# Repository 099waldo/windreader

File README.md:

# WindReader

WindReader is a Raspberry Pi hat for reading sensor data from the NRG #40 Anemometer and the NRG 200P direction vane from NRG Systems. 

It uses the popular LM741 op amp as well as the MCP3008 analog to digital converter in order to send the analog sensor readings 
to the Raspberry Pi.

The project started when I scored some free wind sensors from an old weather station. It seemed like the perfect opprotunity to try 
my hand at pcb design! 

Unfortunatly, upon further inspection, the only direction vane I got didn't work but in theory the circuit should work fine. 
If I am able to get my hands on a working one I will confirm this.

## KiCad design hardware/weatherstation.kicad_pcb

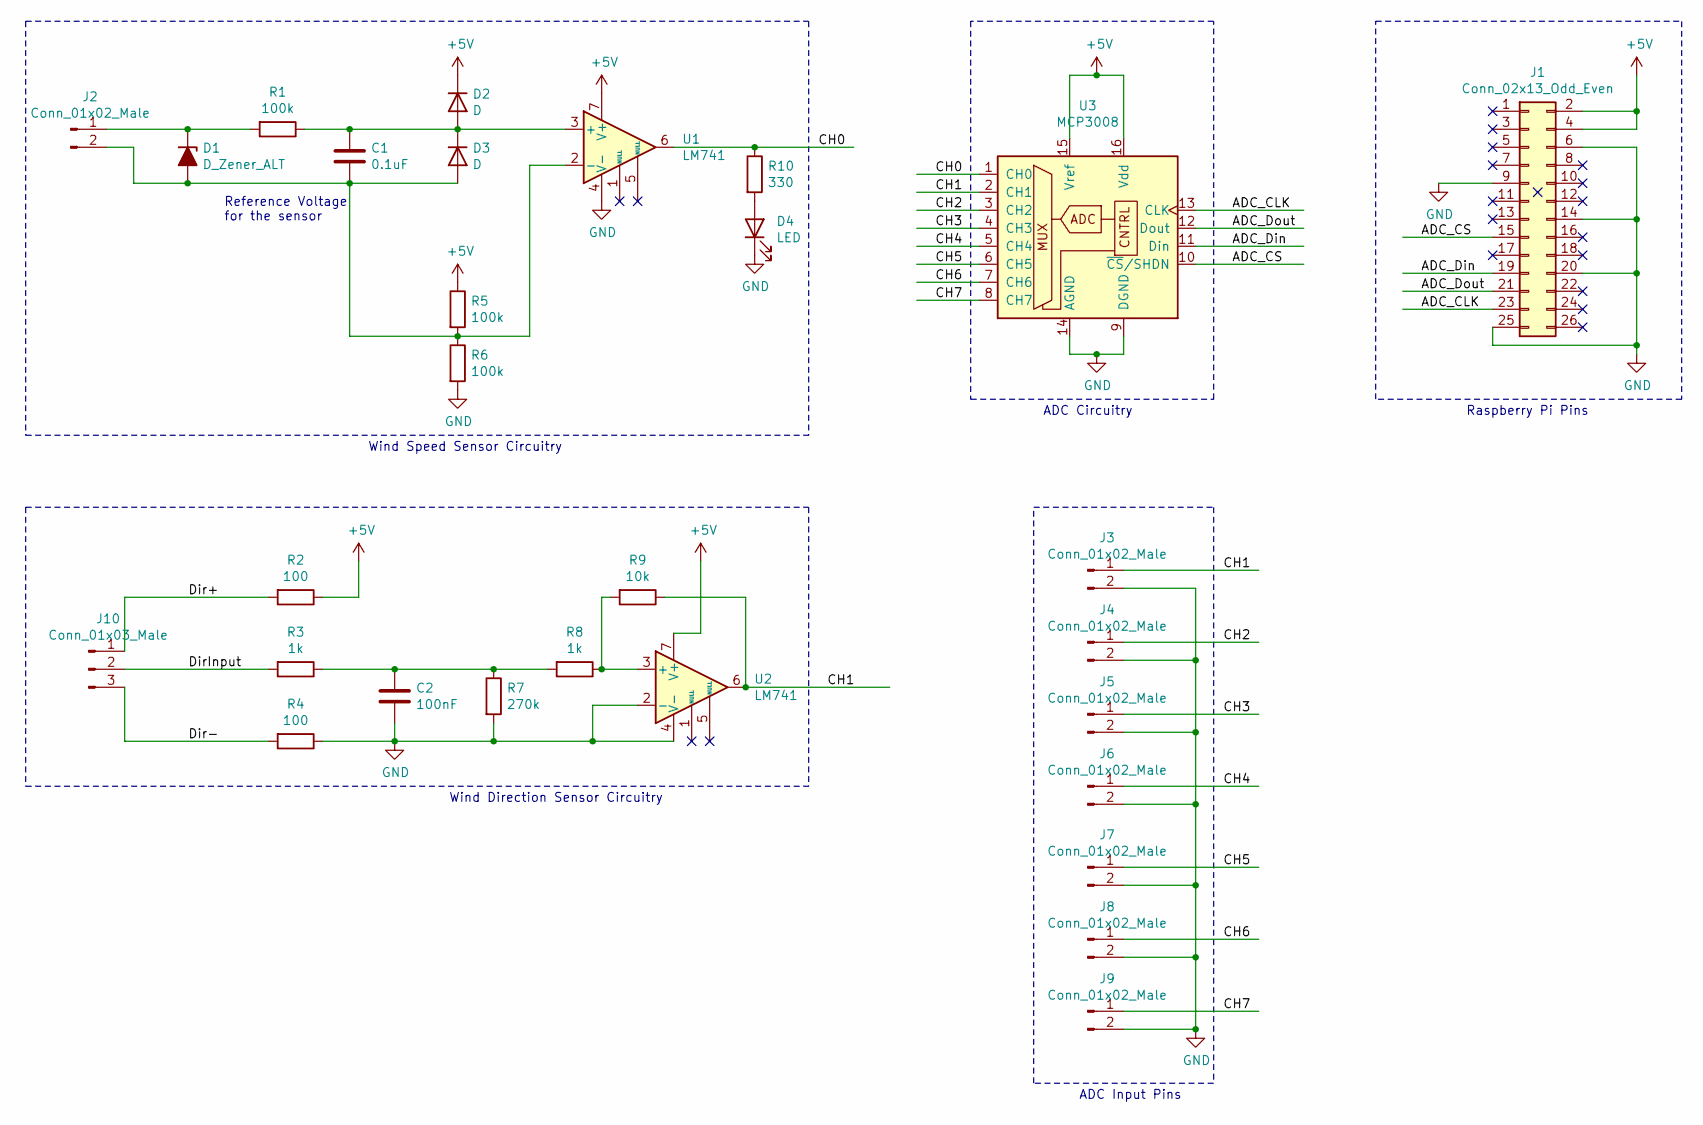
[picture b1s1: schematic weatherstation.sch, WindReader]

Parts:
C1: 0.1uF; CP_Radial_D5.0mm_P2.50mm
C2: 100nF; C_Rect_L4.0mm_W2.5mm_P2.50mm
D1: D_Zener_ALT; D_A-405_P7.62mm_Horizontal
D2, D3: D; D_A-405_P7.62mm_Horizontal
D4: LED; LED_D5.0mm
J1: Conn_02x13_Odd_Even; PinHeader_2x13_P2.54mm_Vertical
J2, J3, J4, J5, J6, J7, J8, J9: Conn_01x02_Male; PinHeader_1x02_P2.54mm_Vertical
J10: Conn_01x03_Male; PinHeader_1x03_P2.54mm_Vertical
R1, R5, R6: 100k; R_Axial_DIN0207_L6.3mm_D2.5mm_P10.16mm_Horizontal
R2, R4: 100; R_Axial_DIN0207_L6.3mm_D2.5mm_P10.16mm_Horizontal
R3, R8: 1k; R_Axial_DIN0207_L6.3mm_D2.5mm_P10.16mm_Horizontal
R7: 270k; R_Axial_DIN0207_L6.3mm_D2.5mm_P10.16mm_Horizontal
R9: 10k; R_Axial_DIN0207_L6.3mm_D2.5mm_P10.16mm_Horizontal
R10: 330; R_Axial_DIN0207_L6.3mm_D2.5mm_P10.16mm_Horizontal
U1, U2: LM741; DIP-8_W7.62mm
U3: MCP3008; DIP-16_W7.62mm

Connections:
+5V: D2.1 (K), J1.2, J1.4, R2.1, R5.1, U1.7 (V+), U2.7 (V+), U3.15 (Vref), U3.16 (Vdd)
/ADC_CLK: J1.23, U3.13 (CLK)
/ADC_CS: J1.15, U3.10 (~CS~/SHDN)
/ADC_Din: J1.19, U3.11 (Din)
/ADC_Dout: J1.21, U3.12 (Dout)
/CH0: R10.1, U1.6, U3.1 (CH0)
/CH1: J3.1, R9.1, U2.6, U3.2 (CH1)
/CH2: J4.1, U3.3 (CH2)
/CH3: J5.1, U3.4 (CH3)
/CH4: J6.1, U3.5 (CH4)
/CH5: J7.1, U3.6 (CH5)
/CH6: J8.1, U3.7 (CH6)
/CH7: J9.1, U3.8 (CH7)
/Dir+: J10.1, R2.2
/Dir-: J10.3, R4.2
/DirInput: J10.2, R3.2
GND: C2.2, D4.1 (K), J1.6, J1.9, J1.14, J1.20, J1.25, J3.2, J4.2, J5.2, J6.2, J7.2, J8.2, J9.2, R4.1, R6.2, R7.2, U1.4 (V-), U2.2 (-), U2.4 (V-), U3.9 (DGND), U3.14 (AGND)
unnamed: C1.1, D2.2 (A), D3.1 (K), R1.1, U1.3 (+)
unnamed: C1.2, D1.2 (A), D3.2 (A), J2.2, R5.2, R6.1, U1.2 (-)
unnamed: C2.1, R3.1, R7.1, R8.2
unnamed: D1.1 (K), J2.1, R1.2
unnamed: D4.2 (A), R10.2
unnamed: R8.1, R9.2, U2.3 (+)

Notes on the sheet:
Reference Voltage for the sensor
Wind Speed Sensor Circuitry
Raspberry Pi Pins
ADC Circuitry
Wind Direction Sensor Circuitry
ADC Input Pins

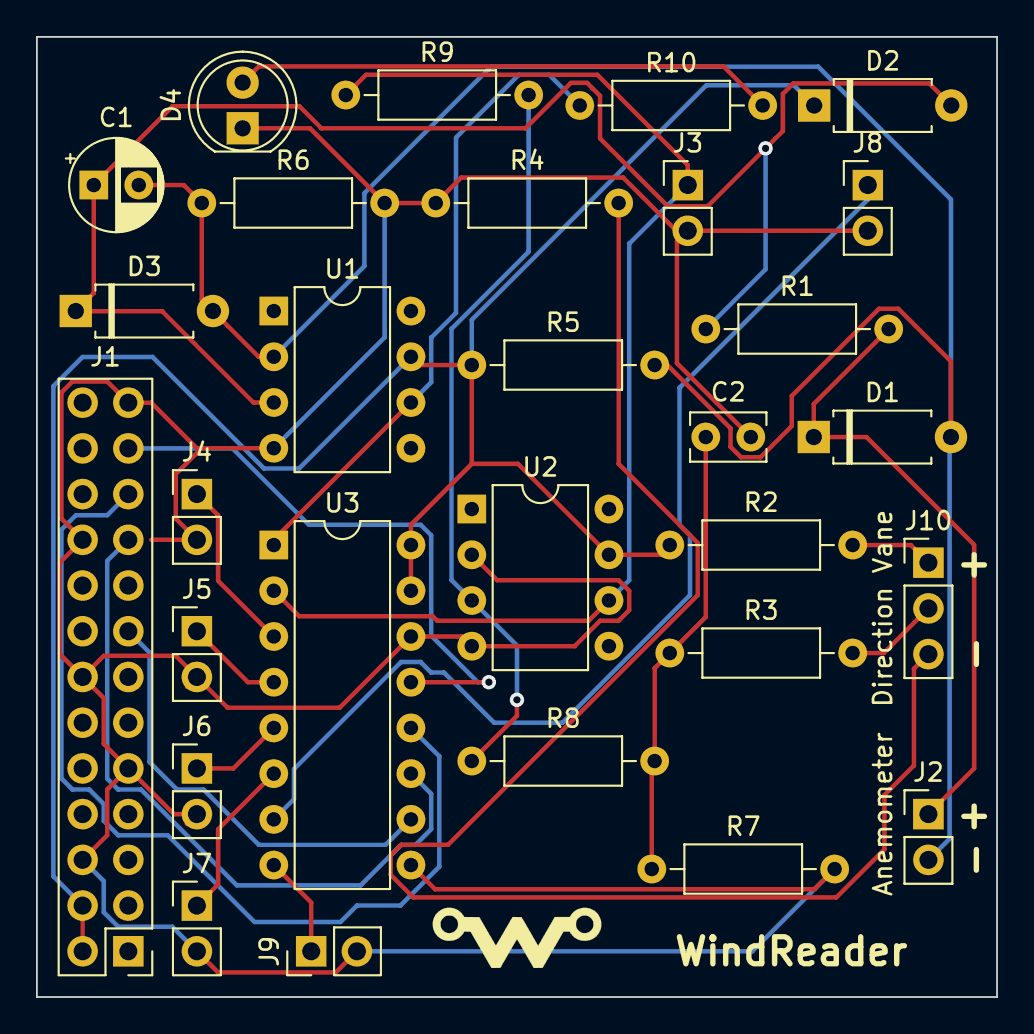
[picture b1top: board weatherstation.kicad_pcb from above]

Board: 2 copper layers, 53.3 x 53.3 mm, 29 parts (0 on the bottom side), 23 nets.

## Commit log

2021-06-08 Updated schematic
2021-06-12 Finallized schematic
2021-06-12 Added input for speed direction circuitry
2021-06-13 Added footprints to schematic and generated netlist
2021-06-13 Added resistor datasheet
2021-06-13 Finished first pcb layout
2021-06-13 Added first layout on silkscreen
2021-06-24 Added second layout
2021-06-25 Added logo. Tidied up a bit
2021-06-25 Changed name
2021-06-25 Added gitignore
2021-06-25 Fixed backwards raspi header
2021-06-25 Moved component label back onto pcb
2021-06-25 Added place for jlc order number
2021-06-25 Generated Gerbers and ordered from JLC
2021-07-04 Finallized schematic exported to pdf
2021-07-10 Added forgotten component values
2021-07-10 Reorganized repo
2021-07-11 Got demo file working
2021-07-17 Fixed ground of anemometer going ground problem
2021-07-17 Added images
2021-07-17 Changed to slightly better images
2021-07-18 Callibrated sensor
